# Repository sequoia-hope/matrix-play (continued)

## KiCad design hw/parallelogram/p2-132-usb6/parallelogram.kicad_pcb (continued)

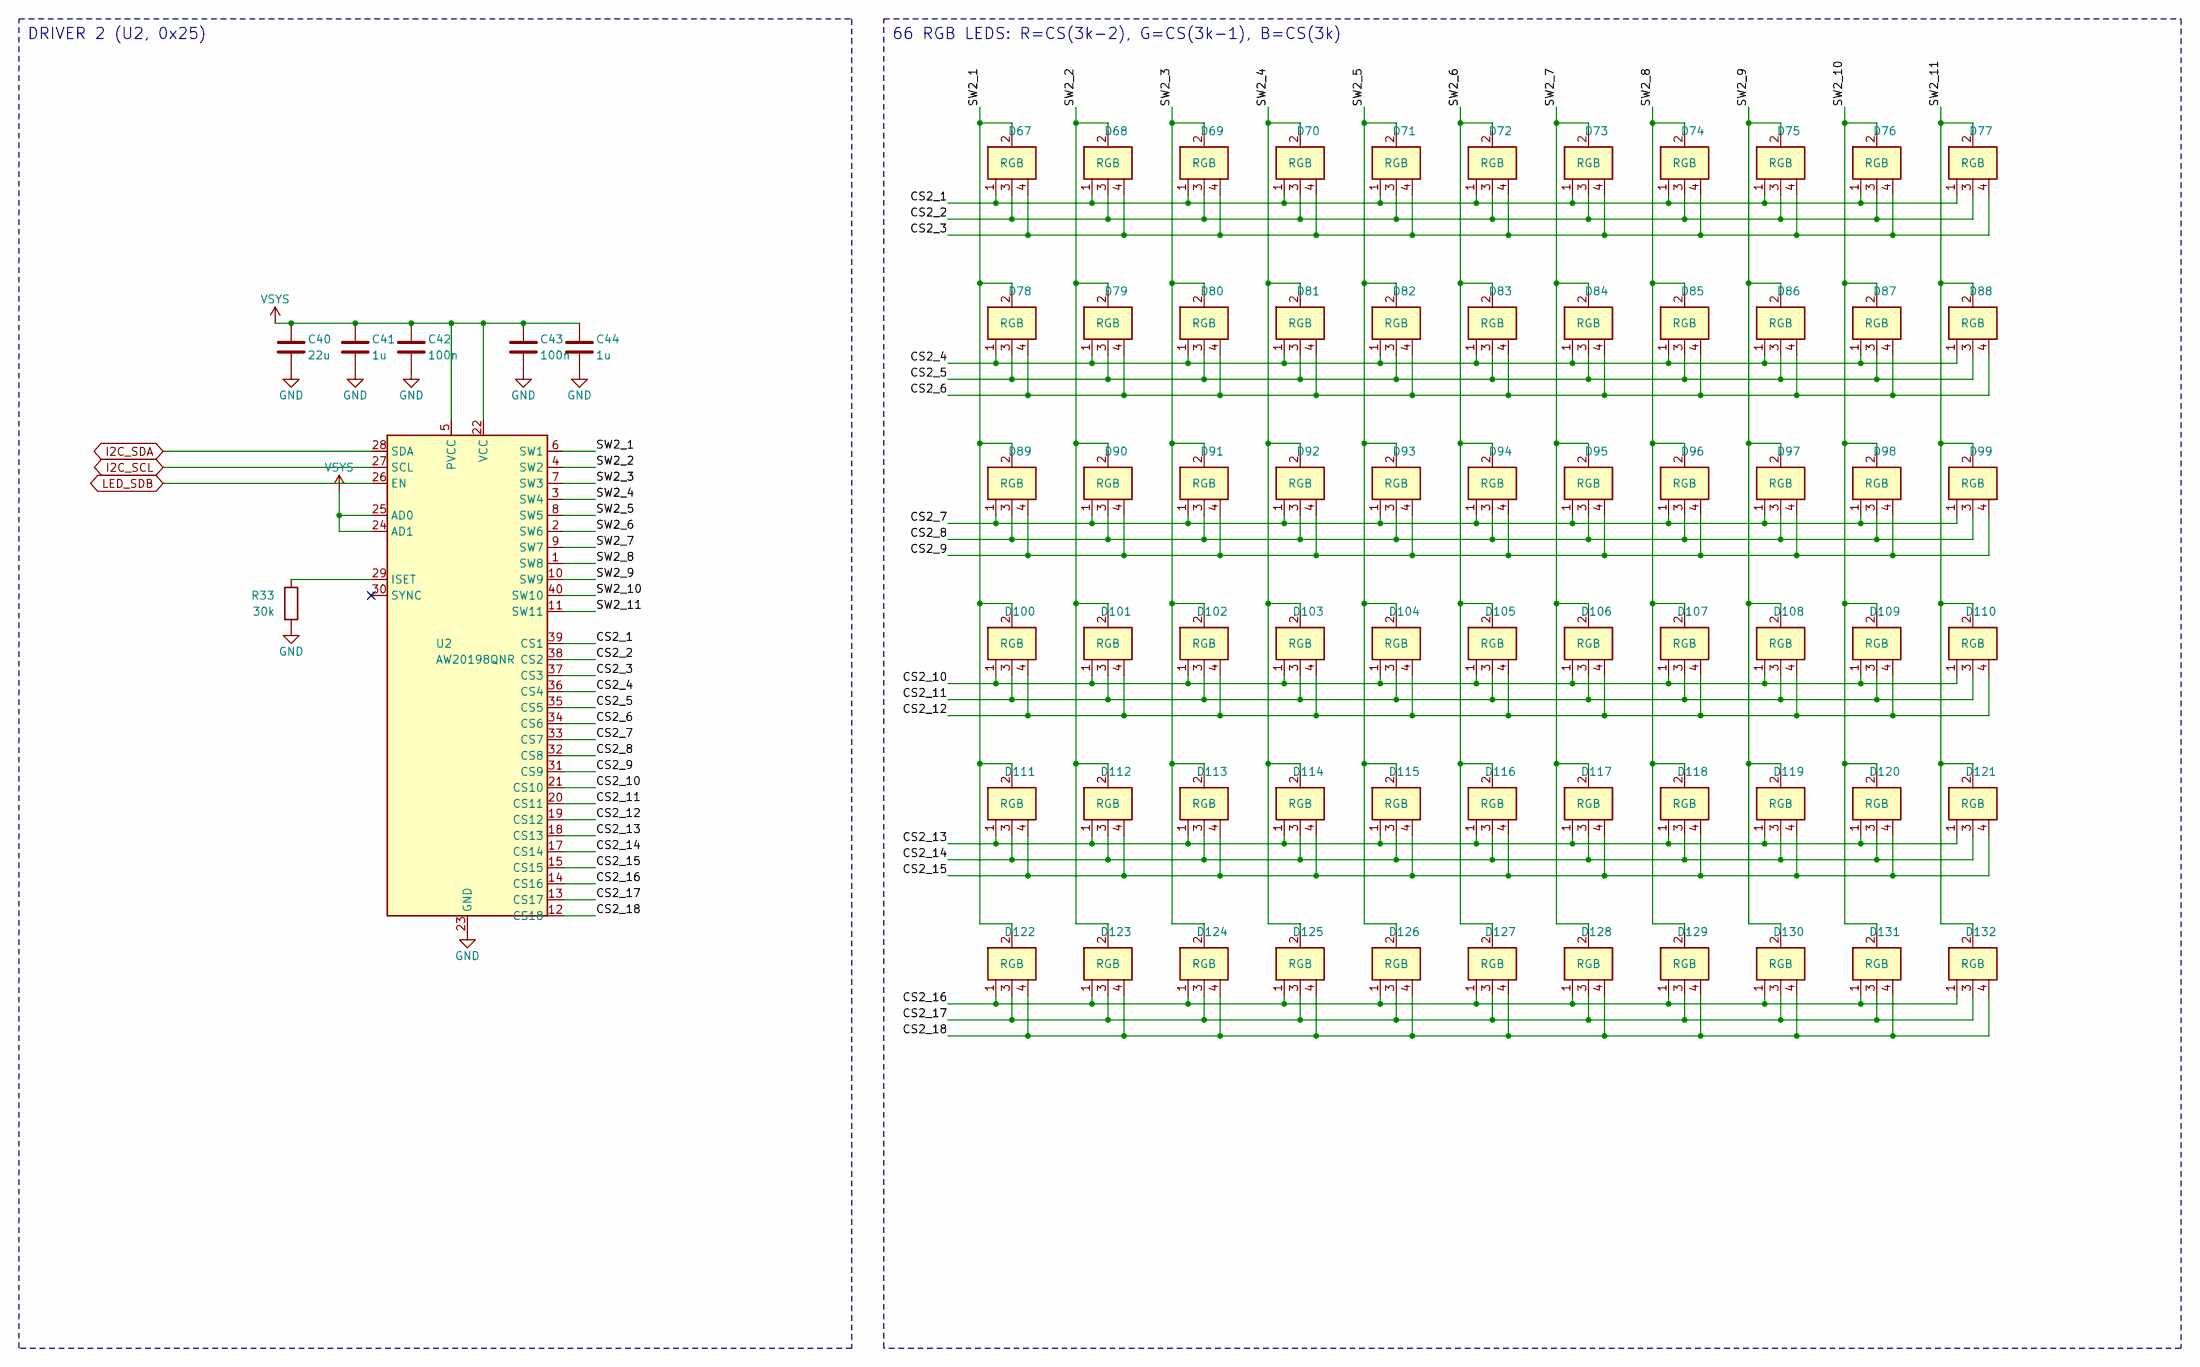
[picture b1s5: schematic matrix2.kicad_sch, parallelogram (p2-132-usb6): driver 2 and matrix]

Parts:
C40: 22u; C_0603_1608Metric; MPN CL10A226MP8NUNE; LCSC C86295
C41, C44: 1u; C_0402_1005Metric; MPN CL05A105KA5NQNC; LCSC C52923
C42, C43: 100n; C_0402_1005Metric; MPN CL05B104KO5NNNC; LCSC C1525
D67, D68, D69, D70, D71, D72, D73, D74, D75, D76, D77, D78, D79, D80, D81, D82, D83, D84, D85, D86, D87, D88, D89, D90, D91, D92, D93, D94, D95, D96, D97, D98, D99, D100, D101, D102, D103, D104, D105, D106, D107, D108, D109, D110, D111, D112, D113, D114, D115, D116, D117, D118, D119, D120, D121, D122, D123, D124, D125, D126, D127, D128, D129, D130, D131, D132: RGB; LED_XL-1615RGBC; MPN XL-1615RGBC-RF; LCSC C965840
R33: 30k; R_0402_1005Metric; MPN 0402WGF3002TCE; LCSC C25776
U2: AW20198QNR; AW20198_QFN-40-1EP_5x5mm_P0.4mm_EP3.4x3.4mm; MPN AW20198QNR; LCSC C5137654

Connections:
/Driver 2 and matrix/CS2_1: D67.1 (R), D68.1 (R), D69.1 (R), D70.1 (R), D71.1 (R), D72.1 (R), D73.1 (R), D74.1 (R), D75.1 (R), D76.1 (R), D77.1 (R), U2.39 (CS1)
/Driver 2 and matrix/CS2_2: D67.3 (G), D68.3 (G), D69.3 (G), D70.3 (G), D71.3 (G), D72.3 (G), D73.3 (G), D74.3 (G), D75.3 (G), D76.3 (G), D77.3 (G), U2.38 (CS2)
/Driver 2 and matrix/CS2_3: D67.4 (B), D68.4 (B), D69.4 (B), D70.4 (B), D71.4 (B), D72.4 (B), D73.4 (B), D74.4 (B), D75.4 (B), D76.4 (B), D77.4 (B), U2.37 (CS3)
/Driver 2 and matrix/CS2_4: D78.1 (R), D79.1 (R), D80.1 (R), D81.1 (R), D82.1 (R), D83.1 (R), D84.1 (R), D85.1 (R), D86.1 (R), D87.1 (R), D88.1 (R), U2.36 (CS4)
/Driver 2 and matrix/CS2_5: D78.3 (G), D79.3 (G), D80.3 (G), D81.3 (G), D82.3 (G), D83.3 (G), D84.3 (G), D85.3 (G), D86.3 (G), D87.3 (G), D88.3 (G), U2.35 (CS5)
/Driver 2 and matrix/CS2_6: D78.4 (B), D79.4 (B), D80.4 (B), D81.4 (B), D82.4 (B), D83.4 (B), D84.4 (B), D85.4 (B), D86.4 (B), D87.4 (B), D88.4 (B), U2.34 (CS6)
/Driver 2 and matrix/CS2_7: D89.1 (R), D90.1 (R), D91.1 (R), D92.1 (R), D93.1 (R), D94.1 (R), D95.1 (R), D96.1 (R), D97.1 (R), D98.1 (R), D99.1 (R), U2.33 (CS7)
/Driver 2 and matrix/CS2_8: D89.3 (G), D90.3 (G), D91.3 (G), D92.3 (G), D93.3 (G), D94.3 (G), D95.3 (G), D96.3 (G), D97.3 (G), D98.3 (G), D99.3 (G), U2.32 (CS8)
/Driver 2 and matrix/CS2_9: D89.4 (B), D90.4 (B), D91.4 (B), D92.4 (B), D93.4 (B), D94.4 (B), D95.4 (B), D96.4 (B), D97.4 (B), D98.4 (B), D99.4 (B), U2.31 (CS9)
/Driver 2 and matrix/CS2_10: D100.1 (R), D101.1 (R), D102.1 (R), D103.1 (R), D104.1 (R), D105.1 (R), D106.1 (R), D107.1 (R), D108.1 (R), D109.1 (R), D110.1 (R), U2.21 (CS10)
/Driver 2 and matrix/CS2_11: D100.3 (G), D101.3 (G), D102.3 (G), D103.3 (G), D104.3 (G), D105.3 (G), D106.3 (G), D107.3 (G), D108.3 (G), D109.3 (G), D110.3 (G), U2.20 (CS11)
/Driver 2 and matrix/CS2_12: D100.4 (B), D101.4 (B), D102.4 (B), D103.4 (B), D104.4 (B), D105.4 (B), D106.4 (B), D107.4 (B), D108.4 (B), D109.4 (B), D110.4 (B), U2.19 (CS12)
/Driver 2 and matrix/CS2_13: D111.1 (R), D112.1 (R), D113.1 (R), D114.1 (R), D115.1 (R), D116.1 (R), D117.1 (R), D118.1 (R), D119.1 (R), D120.1 (R), D121.1 (R), U2.18 (CS13)
/Driver 2 and matrix/CS2_14: D111.3 (G), D112.3 (G), D113.3 (G), D114.3 (G), D115.3 (G), D116.3 (G), D117.3 (G), D118.3 (G), D119.3 (G), D120.3 (G), D121.3 (G), U2.17 (CS14)
/Driver 2 and matrix/CS2_15: D111.4 (B), D112.4 (B), D113.4 (B), D114.4 (B), D115.4 (B), D116.4 (B), D117.4 (B), D118.4 (B), D119.4 (B), D120.4 (B), D121.4 (B), U2.15 (CS15)
/Driver 2 and matrix/CS2_16: D122.1 (R), D123.1 (R), D124.1 (R), D125.1 (R), D126.1 (R), D127.1 (R), D128.1 (R), D129.1 (R), D130.1 (R), D131.1 (R), D132.1 (R), U2.14 (CS16)
/Driver 2 and matrix/CS2_17: D122.3 (G), D123.3 (G), D124.3 (G), D125.3 (G), D126.3 (G), D127.3 (G), D128.3 (G), D129.3 (G), D130.3 (G), D131.3 (G), D132.3 (G), U2.13 (CS17)
/Driver 2 and matrix/CS2_18: D122.4 (B), D123.4 (B), D124.4 (B), D125.4 (B), D126.4 (B), D127.4 (B), D128.4 (B), D129.4 (B), D130.4 (B), D131.4 (B), D132.4 (B), U2.12 (CS18)
/Driver 2 and matrix/SW2_1: D67.2 (A), D78.2 (A), D89.2 (A), D100.2 (A), D111.2 (A), D122.2 (A), U2.6 (SW1)
/Driver 2 and matrix/SW2_2: D68.2 (A), D79.2 (A), D90.2 (A), D101.2 (A), D112.2 (A), D123.2 (A), U2.4 (SW2)
/Driver 2 and matrix/SW2_3: D69.2 (A), D80.2 (A), D91.2 (A), D102.2 (A), D113.2 (A), D124.2 (A), U2.7 (SW3)
/Driver 2 and matrix/SW2_4: D70.2 (A), D81.2 (A), D92.2 (A), D103.2 (A), D114.2 (A), D125.2 (A), U2.3 (SW4)
/Driver 2 and matrix/SW2_5: D71.2 (A), D82.2 (A), D93.2 (A), D104.2 (A), D115.2 (A), D126.2 (A), U2.8 (SW5)
/Driver 2 and matrix/SW2_6: D72.2 (A), D83.2 (A), D94.2 (A), D105.2 (A), D116.2 (A), D127.2 (A), U2.2 (SW6)
/Driver 2 and matrix/SW2_7: D73.2 (A), D84.2 (A), D95.2 (A), D106.2 (A), D117.2 (A), D128.2 (A), U2.9 (SW7)
/Driver 2 and matrix/SW2_8: D74.2 (A), D85.2 (A), D96.2 (A), D107.2 (A), D118.2 (A), D129.2 (A), U2.1 (SW8)
/Driver 2 and matrix/SW2_9: D75.2 (A), D86.2 (A), D97.2 (A), D108.2 (A), D119.2 (A), D130.2 (A), U2.10 (SW9)
/Driver 2 and matrix/SW2_10: D76.2 (A), D87.2 (A), D98.2 (A), D109.2 (A), D120.2 (A), D131.2 (A), U2.40 (SW10)
/Driver 2 and matrix/SW2_11: D77.2 (A), D88.2 (A), D99.2 (A), D110.2 (A), D121.2 (A), D132.2 (A), U2.11 (SW11)
I2C_SCL: U2.27 (SCL); also elsewhere on the board
I2C_SDA: U2.28 (SDA); also elsewhere on the board
LED_SDB: U2.26 (EN); also elsewhere on the board
unnamed: R33.1, U2.29 (ISET)
VSYS: C40.1, C41.1, C42.1, C43.1, C44.1, U2.5 (PVCC), U2.22 (VCC), U2.24 (AD1), U2.25 (AD0); also elsewhere on the board

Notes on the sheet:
DRIVER 2 (U2, 0x25)
66 RGB LEDS: R=CS(3k-2), G=CS(3k-1), B=CS(3k)

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
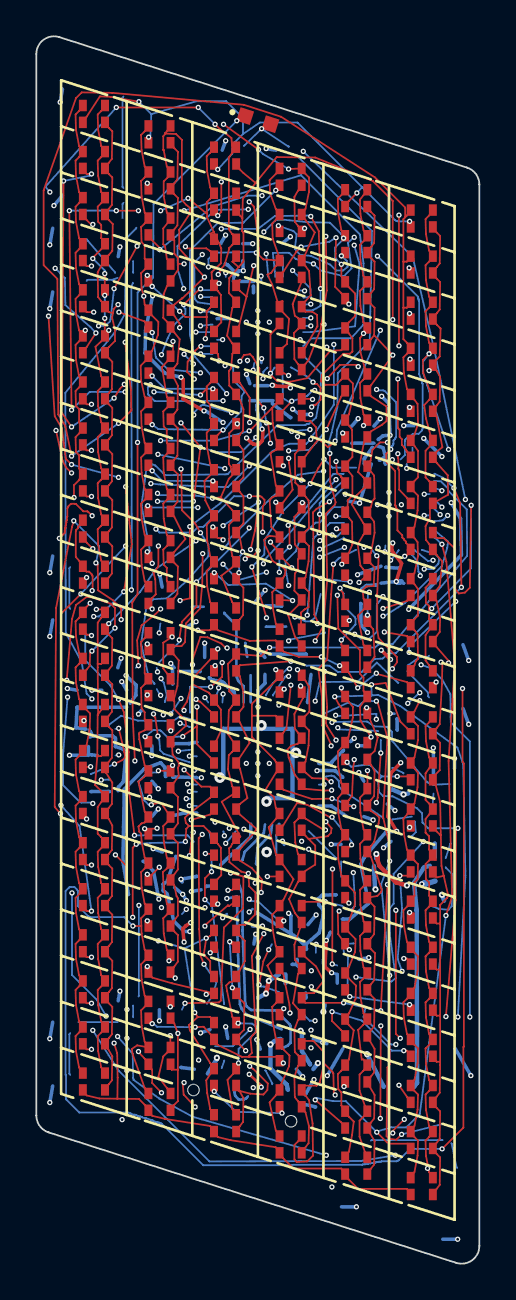
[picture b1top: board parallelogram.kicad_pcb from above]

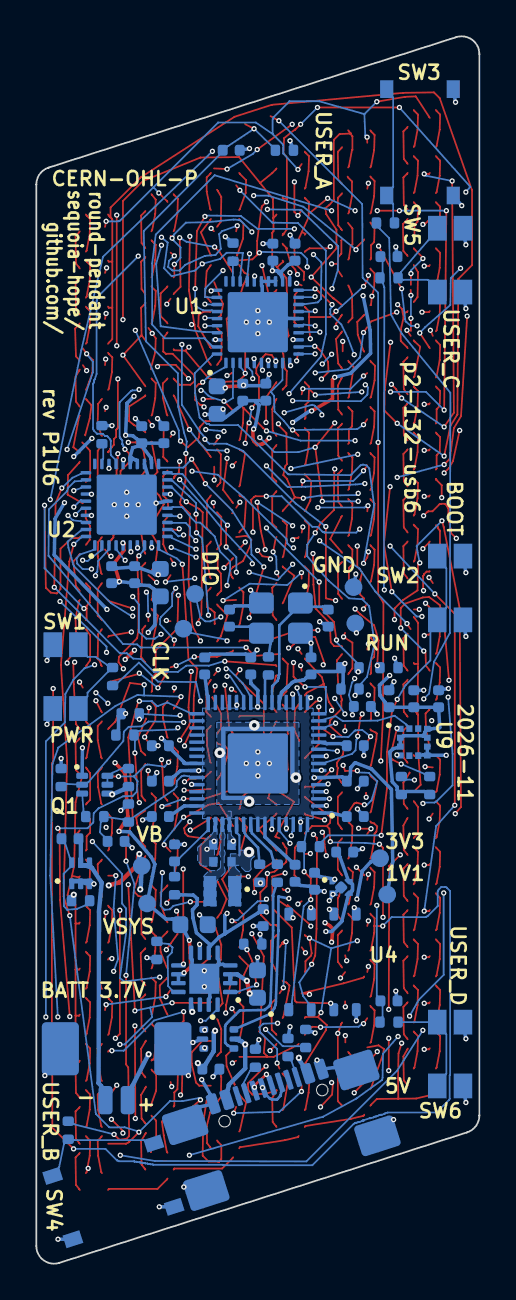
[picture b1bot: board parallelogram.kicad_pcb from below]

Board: 4 copper layers, 25.0 x 69.3 mm, 231 parts (98 on the bottom side), 118 nets.

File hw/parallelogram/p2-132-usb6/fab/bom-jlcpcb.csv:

Comment,Designator,Footprint,LCSC Part #,MPN,Manufacturer
A1251WR-S-2P,BT1,Molex_PicoBlade_53261-0271_1x02-1MP_P1.25mm_Horizontal,C225111,A1251WR-S-2P,CJT
1u,"C1,C3,C4,C31,C34,C41,C44",C_0402_1005Metric,C52923,CL05A105KA5NQNC,Samsung Electro-Mechanics
22u,"C2,C30,C40",C_0603_1608Metric,C86295,CL10A226MP8NUNE,Samsung Electro-Mechanics
10u,C5,C_0603_1608Metric,C19702,CL10A106KP8NNNC,Samsung Electro-Mechanics
100n,"C6,C7,C8,C9,C10,C11,C12,C13,C14,C20,C21,C22,C25,C27,C32,C33,C35,C42,C43,C70",C_0402_1005Metric,C1525,CL05B104KO5NNNC,Samsung Electro-Mechanics
4.7u,"C16,C18",C_0402_1005Metric_small_pads,C23733,CL05A475MP5NRNC,Samsung Electro-Mechanics
4.7u,"C17,C19,C26",C_0402_1005Metric,C23733,CL05A475MP5NRNC,Samsung Electro-Mechanics
15p,"C23,C24",C_0402_1005Metric,C1548,0402CG150J500NT,FH
100n,"C71,C72",C_0402_1005Metric,C307331,CL05B104KB54PNC,Samsung Electro-Mechanics
RGB,"D1,D2,D3,D4,D5,D6,D7,D8,D9,D10,D11,D12,D13,D14,D15,D16,D17,D18,D19,D20,D21,D22,D23,D24,D25,D26,D27,D28,D29,D30,D31,D32,D33,D34,D35,D36,D37,D38,D39,D40,D41,D42,D43,D44,D45,D46,D47,D48,D49,D50,D51,D52,D53,D54,D55,D56,D57,D58,D59,D60,D61,D62,D63,D64,D65,D66,D67,D68,D69,D70,D71,D72,D73,D74,D75,D76,D77,D78,D79,D80,D81,D82,D83,D84,D85,D86,D87,D88,D89,D90,D91,D92,D93,D94,D95,D96,D97,D98,D99,D100,D101,D102,D103,D104,D105,D106,D107,D108,D109,D110,D111,D112,D113,D114,D115,D116,D117,D118,D119,D120,D121,D122,D123,D124,D125,D126,D127,D128,D129,D130,D131,D132",LED_XL-1615RGBC,C965840,XL-1615RGBC-RF,XINGLIGHT
TYPE-C-31-M-22,J1,USB_C_Receptacle_Hroparts_TYPE-C-31-M-22,C530612,TYPE-C-31-M-22,Korean Hroparts Elec
3.3u,L1,L_pol_2016,C42411119,AOTA-B201610S3R3-101-T,Abracon
NTZD3155C,Q1,SOT-563,C236117,NTZD3155CT1G,onsemi
XYC-PT19C-L1,Q2,SENSOR_ALS-PT19,C2693594,XYC-PT19C-L1,NEWOPTO
5.1k,"R1,R2",R_0402_1005Metric,C25905,0402WGF5101TCE,UNI-ROYAL
10k,R3,R_0402_1005Metric,C25744,0402WGF1002TCE,UNI-ROYAL
3k,R4,R_0402_1005Metric,C25784,0402WGF3001TCE,UNI-ROYAL
3.6k,R5,R_0402_1005Metric,C25891,0402WGF3601TCE,UNI-ROYAL
100k,"R6,R7,R9,R10,R11,R12,R31",R_0402_1005Metric,C25741,0402WGF1003TCE,UNI-ROYAL
100R,R8,R_0402_1005Metric,C25076,0402WGF1000TCE,UNI-ROYAL
33R,R13,R_0402_1005Metric,C25105,0402WGF330JTCE,UNI-ROYAL
27R,"R14,R15",R_0402_1005Metric,C25100,0402WGF270JTCE,UNI-ROYAL
1k,"R16,R17,R18,R21,R22,R44,R45,R46,R47",R_0402_1005Metric,C11702,0402WGF1001TCE,UNI-ROYAL
4.7k,"R19,R20",R_0402_1005Metric,C25900,0402WGF4701TCE,UNI-ROYAL
30k,"R30,R33",R_0402_1005Metric,C25776,0402WGF3002TCE,UNI-ROYAL
22k,R43,R_0402_1005Metric,C25768,0402WGF2202TCE,UNI-ROYAL
USER / WAKE,SW1,SW_Panasonic_EVQP7J,C2828254,EVQP7J01P,PANASONIC
BOOTSEL,SW2,SW_Panasonic_EVQP7J,C2828254,EVQP7J01P,PANASONIC
NW WING,SW3,SW_Push_1P1T_XKB_TS-1187A,C318884,TS-1187A-B-A-B,XKB Connection
SE WING,SW4,SW_Push_1P1T_XKB_TS-1187A,C318884,TS-1187A-B-A-B,XKB Connection
USER_C (WEST N),SW5,SW_Panasonic_EVQP7J,C2828254,EVQP7J01P,PANASONIC
USER_D (WEST S),SW6,SW_Panasonic_EVQP7J,C2828254,EVQP7J01P,PANASONIC
AW20198QNR,"U1,U2",AW20198_QFN-40-1EP_5x5mm_P0.4mm_EP3.4x3.4mm,C5137654,AW20198QNR,Shanghai Awinic Tech
RP2350A,U3,RP2350-QFN-60-1EP_7x7_P0.4mm_EP3.4x3.4mm_ThermalVias,C42411118,RP2350A,Raspberry Pi
W25Q128JVPIQ,U4,WSON-8_6x5mm_P1.27mm_NoEPCopper,C190862,W25Q128JVPIQ,Winbond
BQ24073,U5,QFN-16-1EP_3x3mm_P0.5mm_EP1.7x1.7mm,C15220,BQ24073RGTR,Texas Instruments
TPS7A0233,U6,Texas_X2SON-4_1x1mm_P0.65mm,C2860046,TPS7A0233PDQNR,Texas Instruments
USBLC6-2P6,U7,SOT-666,C15999,USBLC6-2P6,STMicroelectronics
XB9901A,U8,XySemi_DFN-6_1.8x1.4mm,C669687,XB9901A,XySemi
LIS2DW12,U9,LGA-12_2x2mm_P0.5mm,C189624,LIS2DW12TR,STMicroelectronics
12MHz,Y1,Crystal_SMD_3225-4Pin_3.2x2.5mm,C20625731,ABM8-272-T3,Abracon
